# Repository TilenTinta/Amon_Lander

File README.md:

# Amon Lander Project

**Project Status:** In Progress

**Short description:** An open‑source EDF‑hovering lander/hopper inspired by **Sprite** (BPS.space)

> Part of the Amon Lander project:
>
> - **Amon Board** — flight controller hardware & firmware  
>   https://github.com/TilenTinta/Amon_Board
> - **Amon Link** — PC - drone RF bridge (PCB & firmware)  
>   https://github.com/TilenTinta/Amon_Link
> - **Amon Ground Control** — desktop GCS for telemetry & control  
>   https://github.com/TilenTinta/Amon_GroundControl_Software

---

## Table of Contents

- [Overview](#overview)
- [System Concept](#system-concept)
- [Hardware](#hardware)
  - [Frame](#frame)
  - [LED Boards](#led-boards)
- [Getting Started](#getting-started)
  - [Print & Materials](#print--materials)
  - [Assembly Notes](#assembly-notes)
- [Calibration & Testing](#calibration--testing)
- [Repository Structure](#repository-structure)
- [Roadmap](#roadmap)
- [Status & Disclaimer](#status--disclaimer)
- [License](#license)
- [Acknowledgments](#acknowledgments)

---

## Overview

Amon Lander is an educational lander/hopper platform designed to demonstrate vertical takeoff/landing and attitude control with thrust‑vectoring fins. The project emphasizes **building everything from scratch** and using mostly **free maker‑friendly tools**.

> [!INFO]
> **First integrated flight test:** 30.06.2026
>
> The goal of this flight was to validate the complete system, including the airframe, electronics, communications, protocol, flight controller, and ground station and have some fun!

---

## System Concept

- **Propulsion:** Single **EDF fan** for hover.  
- **Control:** **Four servos** drives fins for stabilization (**TVC**).  
- **Sensing:** Onboard sensors monitor flight parameters.  
- **Flight Computer:** **Custom PCB** handles computation and comms with the ground computer.  
- **Ground Segment:** Desktop app for **monitoring and control**.

> The goal is to learn: electronics, 3D modeling, embedded/desktop software, reading documentation, flight mechanics, and control theory—while having fun. Many things could be done faster or simpler, but this project idea is learning and exploration.

---

## Hardware

### Frame

The frame is inspired by Sprite, with custom ideas and modifications. The entire airframe is provided in **STL** and **STEP** and is printable on a standard **FDM** printer.  
- Early prototypes used **XPETG**; later versions used **LW‑PLA** to reduce weight.  
- Frame on image is **not yet flight‑tested** (at least not autonomous flight).  
- Designed in **Autodesk Fusion 360 (Personal Use license)**.

### LED Boards

Compact PCBs with two LEDs (**red** and **white**) indicate system state. They are mounted on the leg ends and top tubes. Although each LED board has a screw hole, **adhesive is recommended** for attachment.

---

## Getting Started

### Print & Materials

- Slice **STL** parts per your printer’s capabilities.  
- Recommended filaments:
  - **LW‑PLA** (weight savings) or **PETG/XPETG** (durability).  
- Orient parts to maximize strength along load paths (legs, fins, mounts).

### Assembly Notes

- Dry‑fit major components before final fastening/adhesive.  
- Verify servo travel and linkage geometry with power **off** first.  
- Route wiring to avoid EDF ingestion and moving fin linkages.  

---

## Calibration & Testing

- Bench‑test **sensors** and **servo directions** before powering the EDF.  
- Perform staged tests: electronics bring‑up → servo only → tethered hover.  
- Log telemetry and review for oscillations; tune control gains incrementally.  

### Test stand
For each test there is a separate test stand. There are:
- Thrust stand (test of EDF thrust level)
- Servo stand (test of servo rotation)
- One and two DoF stand (test of drone moments and fin deflection effect)

All tests are done with the help of an Arduino Uno board used for collecting data from sensors. At the same time, a connection over UART-USB is established to a drone for direct communication and command transmission. Everything is monitored by Jupyter scripts for easy and quick tests. Results are saved in **.csv** files for easy future analysis.

---

## Control algorithm
The initial plan was to use **Matlab** with **Simulink** to create a complete mathematical model of the drone. After further research, I found that many different methods could be used for controlling a drone like this. After designing the first model in **Simulink** and experimenting with the **Simulink Coder** plugin — with the idea of converting it to standard C code for use on my flight controller — I abandoned this approach. The complete model was then rewritten in **Python** using the **NumPy** library, which is used to test, tune, and further refine the drone model. This same model was subsequently rewritten in **CasADi** style, inheriting the **NumPy** parameters. It is still used in Python, but now with the **acados** framework and optimizer to export the complete control code directly to my MCU/flight controller.

Links to libraries:
- **CasADi**: https://github.com/casadi/casadi
- **acados**: https://github.com/acados/acados

---

## Status & Disclaimer

**In active development.** Designs and documents are evolving; expect changes and rough edges. Exercise caution when testing EDF propulsion and keep bystanders at a safe distance.

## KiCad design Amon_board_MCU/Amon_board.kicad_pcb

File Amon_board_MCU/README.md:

Amon Lander - Flight controller

Flight controler (MCU only version). It is 4-layer PCB with:<br />
- Grounged mounting holes
- Two XT60 power connectors
- Voltage measuring: board power and EDF battery voltage
- Input protection: reverse polarity protection - diode
- Max. input voltage: 12V (tested)
- Two buck conterters: 3V3 (MCU, sensors...) and 5V (servos) - both are capable of ~5A
- Board can be turned on when battery is connected or with switch wired to terminal 
- Sensors: Gyroscope (MPU6050), Temperature/Pressure/Humidity (BME280), TOF (TOF400C-VL53L1X) connector, Compas (HMC5883L)
- Radios: 2x NRF24L01+PA/LNA (RX-TX)
- GPS: GY-NEO6MV2 connector [same connector used for drone calibration - process described in firmware]
- On board RGB LED for status indication
- PWM: 4x servo, 1x EDF (can be configured differently)
- Additional external connectors for SPI and I2C devices
- MCU: STM32F405RGT6-LQFP64
- External flash for saving telemetry data
- SD card holder (additional data storing device)
- 10-pin JTAG programming connector
- USB OTG with surge protection

*PCB works but it will be replaced/upgraded to a newer version.

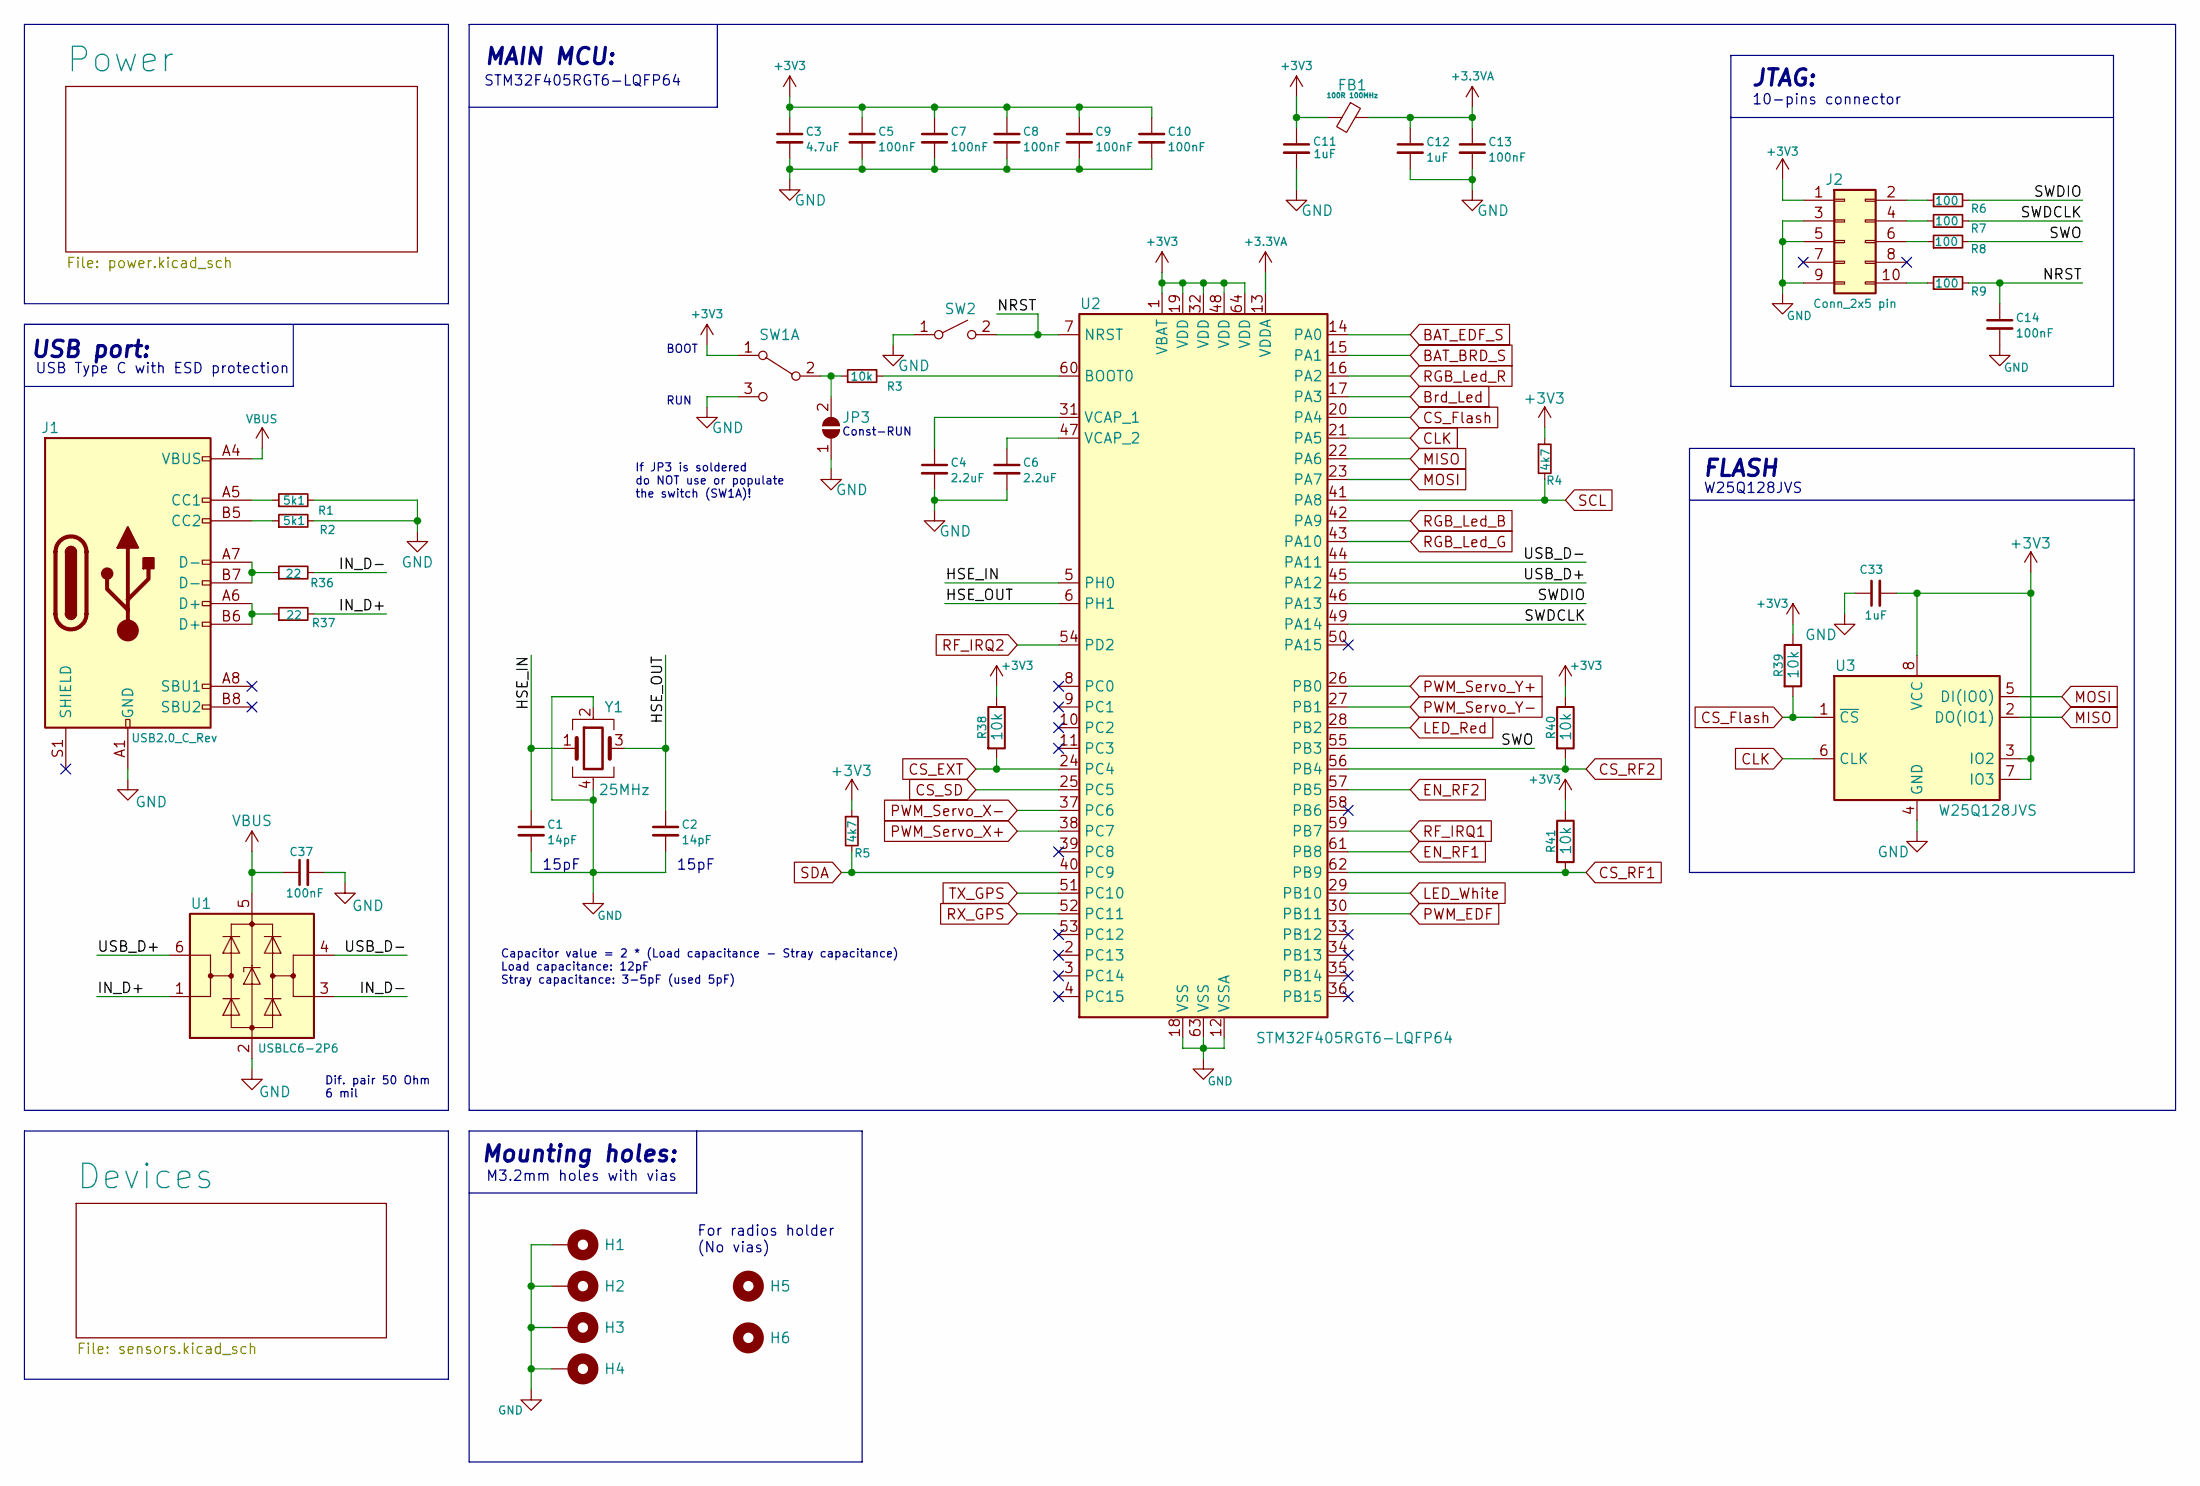
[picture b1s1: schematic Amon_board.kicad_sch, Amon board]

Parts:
C1, C2: 14pF; C_0603_1608Metric
C3: 4.7uF; C_0603_1608Metric
C4, C6: 2.2uF; C_0603_1608Metric
C5, C7, C8, C9, C10, C13, C14, C37: 100nF; C_0603_1608Metric
C11, C12, C33: 1uF; C_0603_1608Metric
FB1: 100R 100MHz; L_1206_3216Metric_Pad1.22x1.90mm_HandSolder
H1, H2, H3, H4: MountingHole_Pad; MountingHole_3.2mm_M3_Pad_Via
H5, H6: MountingHole; MountingHole_3.2mm_M3
J1: USB2.0_C_Rev; USB_C_Receptacle_XKB_U262-16XN-4BVC11
J2: Conn_2x5 pin; IDC-Header_2x05_P2.54mm_Vertical
JP3: SolderJumper_2_Open; SolderJumper-2_P1.3mm_Open_TrianglePad1.0x1.5mm
R1, R2: 5k1; R_0603_1608Metric
R3, R38, R39, R40, R41: 10k; R_0603_1608Metric
R4, R5: 4k7; R_0603_1608Metric
R6, R7, R8, R9: 100; R_0603_1608Metric
R36, R37: 22; R_0603_1608Metric
SW1: SW_DPDT; SW_SPDT_PCM12
SW2: SW_SPST; SW_Push_1P1T_NO_CK_KMR2
U1: USBLC6-2P6; SOT-23-6_Handsoldering
U2: STM32F405RGT6-LQFP64; LQFP-64_10x10mm_P0.5mm
U3: W25Q128JVS; SOIC-8_5.23x5.23mm_P1.27mm
Y1: 25MHz; Crystal_SMD_3225-4Pin_3.2x2.5mm

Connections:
+3.3VA: C12.1, C13.1, FB1.1, U2.13 (VDDA)
+3V3: C3.1, C5.1, C7.1, C8.1, C9.1, C10.1, C11.1, C33.2, FB1.2, J2.1, R4.1, R5.1, R38.1, R39.1, R40.1, R41.1, SW1.1 (A), U2.1 (VBAT), U2.19 (VDD), U2.32 (VDD), U2.48 (VDD), U2.64 (VDD), U3.3 (IO2), U3.7 (IO3), U3.8 (VCC); also elsewhere on the board
/HSE_IN: C1.1, U2.5 (PH0), Y1.1
/HSE_OUT: C2.1, U2.6 (PH1), Y1.3
/IN_D+: R37.2, U1.1 (I/O1)
/IN_D-: R36.2, U1.3 (I/O2)
/NRST: C14.1, R9.2, SW2.2 (B), U2.7 (NRST)
/SWDCLK: R7.2, U2.49 (PA14)
/SWDIO: R6.2, U2.46 (PA13)
/SWO: R8.2, U2.55 (PB3)
/USB_D+: U1.6 (I/O1), U2.45 (PA12)
/USB_D-: U1.4 (I/O2), U2.44 (PA11)
BAT_BRD_S: U2.15 (PA1); also elsewhere on the board
BAT_EDF_S: U2.14 (PA0); also elsewhere on the board
Brd_Led: U2.17 (PA3); also elsewhere on the board
CLK: U2.21 (PA5), U3.6 (CLK); also elsewhere on the board
CS_EXT: R38.2, U2.24 (PC4); also elsewhere on the board
CS_Flash: R39.2, U2.20 (PA4), U3.1 (~CS)
CS_RF1: R41.2, U2.62 (PB9); also elsewhere on the board
CS_RF2: R40.2, U2.56 (PB4); also elsewhere on the board
CS_SD: U2.25 (PC5); also elsewhere on the board
EN_RF1: U2.61 (PB8); also elsewhere on the board
EN_RF2: U2.57 (PB5); also elsewhere on the board
GND: C1.2, C2.2, C3.2, C4.2, C5.2, C6.2, C7.2, C8.2, C9.2, C10.2, C11.2, C12.2, C13.2, C14.2, C33.1, C37.2, H1.1, H2.1, H3.1, H4.1, J1.A1 (GND), J1.A12 (GND), J1.B1 (GND), J1.B12 (GND), J2.3, J2.5, J2.9, JP3.1 (A), R1.2, R2.2, SW1.3 (C), SW2.1 (A), U1.2 (GND), U2.12 (VSSA), U2.18 (VSS), U2.63 (VSS), U3.4 (GND), Y1.2, Y1.4; also elsewhere on the board
LED_Red: U2.28 (PB2); also elsewhere on the board
LED_White: U2.29 (PB10); also elsewhere on the board
MISO: U2.22 (PA6), U3.2 (DO(IO1)); also elsewhere on the board
MOSI: U2.23 (PA7), U3.5 (DI(IO0)); also elsewhere on the board
unnamed: J1.A5 (CC1), R1.1
unnamed: J1.B5 (CC2), R2.1
unnamed: J1.A6 (D+), J1.B6 (D+), R37.1
unnamed: J1.A7 (D-), J1.B7 (D-), R36.1
unnamed: J2.2, R6.1
unnamed: J2.4, R7.1
unnamed: J2.6, R8.1
unnamed: J2.10, R9.1
unnamed: JP3.2 (B), R3.1, SW1.2 (B)
unnamed: R3.2, U2.60 (BOOT0)
unnamed: C4.1, U2.31 (VCAP_1)
unnamed: C6.1, U2.47 (VCAP_2)
PWM_EDF: U2.30 (PB11); also elsewhere on the board
PWM_Servo_X+: U2.38 (PC7); also elsewhere on the board
PWM_Servo_X-: U2.37 (PC6); also elsewhere on the board
PWM_Servo_Y+: U2.26 (PB0); also elsewhere on the board
PWM_Servo_Y-: U2.27 (PB1); also elsewhere on the board
RF_IRQ1: U2.59 (PB7); also elsewhere on the board
RF_IRQ2: U2.54 (PD2); also elsewhere on the board
RGB_Led_B: U2.42 (PA9); also elsewhere on the board
RGB_Led_G: U2.43 (PA10); also elsewhere on the board
RGB_Led_R: U2.16 (PA2); also elsewhere on the board
RX_GPS: U2.52 (PC11); also elsewhere on the board
SCL: R4.2, U2.41 (PA8); also elsewhere on the board
SDA: R5.2, U2.40 (PC9); also elsewhere on the board
TX_GPS: U2.51 (PC10); also elsewhere on the board
VBUS: C37.1, J1.A4 (VBUS), J1.A9 (VBUS), J1.B4 (VBUS), J1.B9 (VBUS), U1.5 (VBUS)

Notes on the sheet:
15pF
W25Q128JVS
10-pins connector
If JP3 is soldered do NOT use or populate the switch (SW1A)!
Capacitor value = 2 * (Load capacitance - Stray capacitance) Load capacitance: 12pF Stray capacitance: 3-5pF (used 5pF)
RUN
JTAG:
M3.2mm holes with vias
Dif. pair 50 Ohm 6 mil
USB port:
Const-RUN
FLASH
Mounting holes:
MAIN MCU:
USB Type C with ESD protection
BOOT
For radios holder (No vias)
STM32F405RGT6-LQFP64

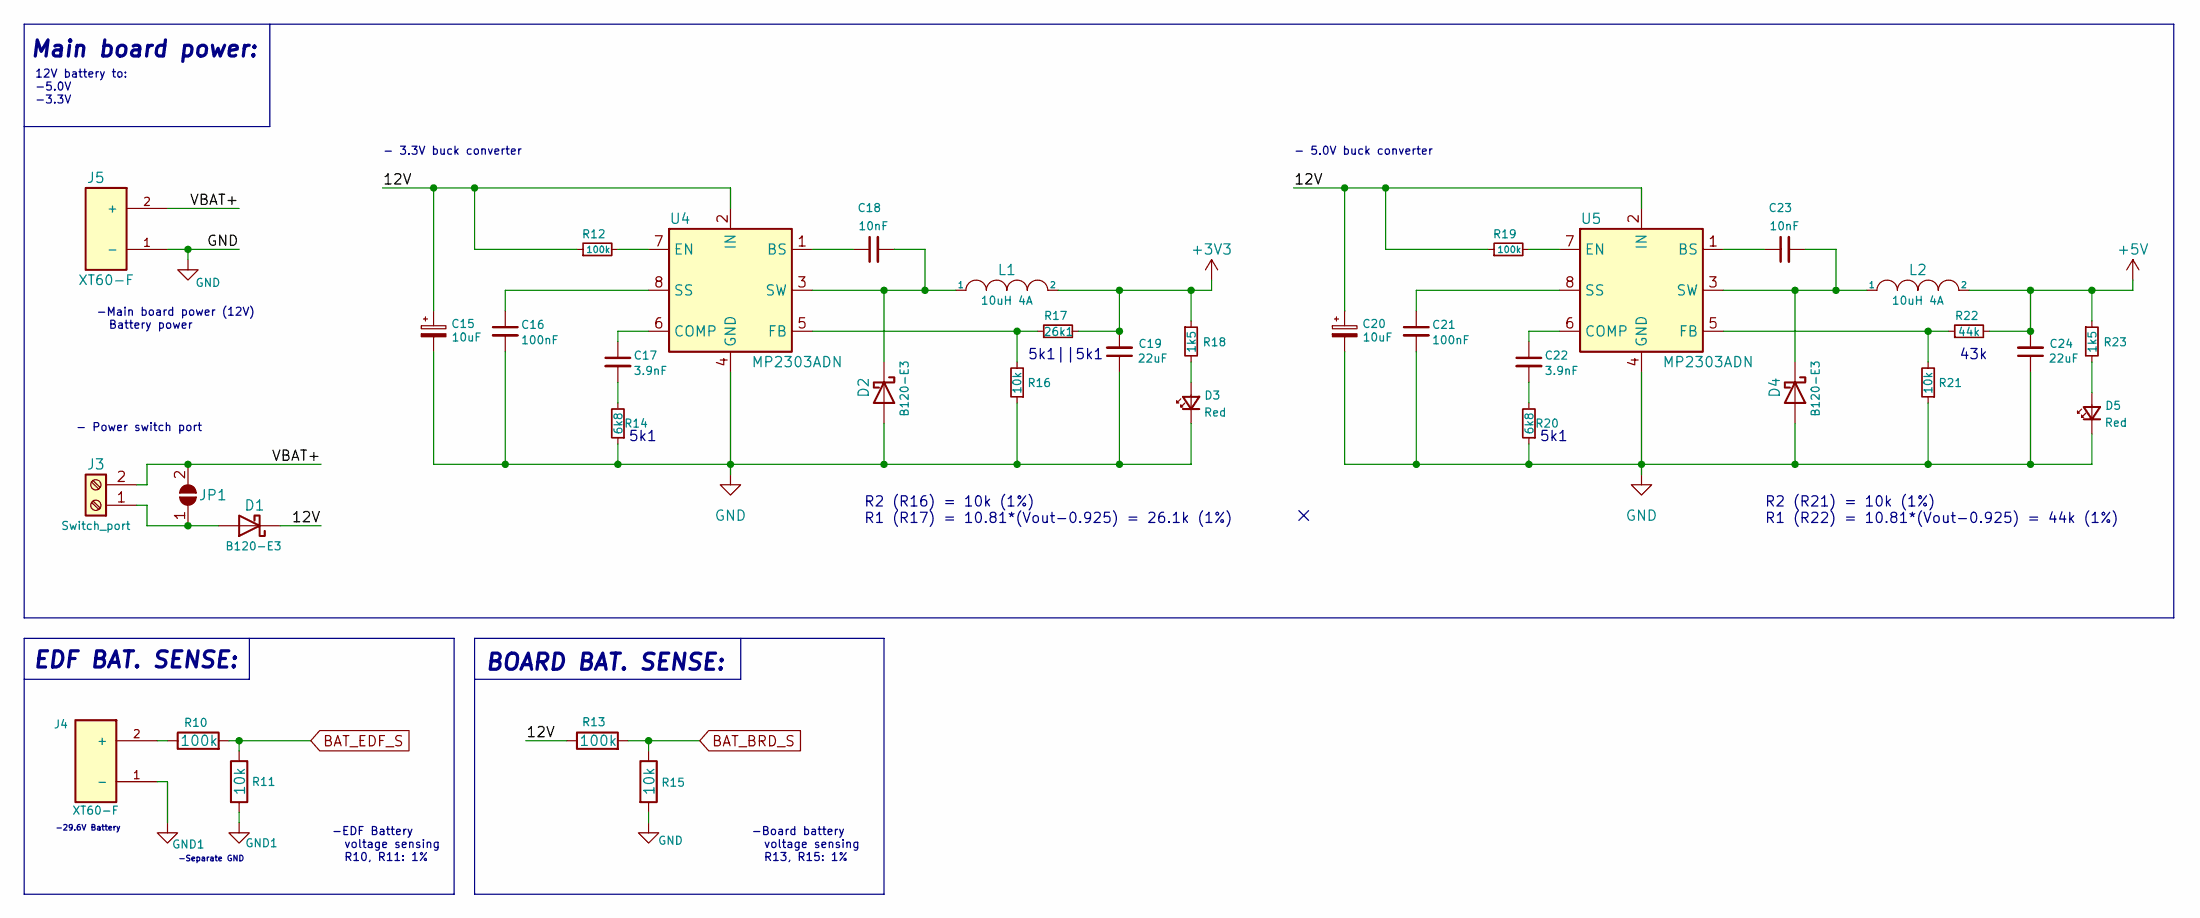
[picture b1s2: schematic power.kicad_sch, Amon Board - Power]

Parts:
C15, C20: 10uF; CP_EIA-3216-10_Kemet-I
C16, C21: 100nF; C_0603_1608Metric
C17, C22: 3.9nF; C_0603_1608Metric
C18, C23: 10nF; C_0603_1608Metric
C19, C24: 22uF; C_1206_3216Metric
D1, D2, D4: B120-E3; D_SMA
D3, D5: Red; LED_0603_1608Metric
J3: Switch_port; TerminalBlock_MetzConnect_Type055_RT01502HDWU_1x02_P5.00mm_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
J4, J5: XT60-F; AMASS_XT60-M; PARTREV 1.2
JP1: SolderJumper_2_Open; SolderJumper-2_P1.3mm_Open_Pad1.0x1.5mm
L1, L2: 10uH 4A; L_10.4x10.4_H4.8
R10, R13: 100k; R_1206_3216Metric
R11, R15: 10k; R_1206_3216Metric
R12, R19: 100k; R_0603_1608Metric
R14, R20: 6k8; R_0603_1608Metric
R16, R21: 10k; R_0603_1608Metric
R17: 26k1; R_0603_1608Metric
R18, R23: 1k5; R_0603_1608Metric
R22: 44k; R_0603_1608Metric
U4, U5: MP2303ADN; SOIC-8-1EP_3.9x4.9mm_P1.27mm_EP2.62x3.51mm

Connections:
+3V3: C19.2, L1.2, R17.2, R18.1; also elsewhere on the board
+5V: C24.2, L2.2, R22.2, R23.1; also elsewhere on the board
/Power/12V: C15.1, C20.1, D1.1 (K), R12.1, R13.1, R19.1, U4.2 (IN), U5.2 (IN)
/Power/VBAT+: J3.2, J5.2 (+), JP1.2 (B)
BAT_BRD_S: R13.2, R15.1; also elsewhere on the board
BAT_EDF_S: R10.2, R11.1; also elsewhere on the board
GND: C15.2, C16.2, C19.1, C20.2, C21.2, C24.1, D2.2 (A), D3.1 (K), D4.2 (A), D5.1 (K), J5.1 (-), R14.1, R15.2, R16.1, R20.1, R21.1, U4.4 (GND), U5.4 (GND); also elsewhere on the board
GND1: J4.1 (-), R11.2
unnamed: C17.2, R14.2
unnamed: C22.2, R20.2
unnamed: D1.2 (A), J3.1, JP1.1 (A)
unnamed: C18.2, D2.1 (K), L1.1, U4.3 (SW)
unnamed: D3.2 (A), R18.2
unnamed: C23.2, D4.1 (K), L2.1, U5.3 (SW)
unnamed: D5.2 (A), R23.2
unnamed: J4.2 (+), R10.1
unnamed: C18.1, U4.1 (BS)
unnamed: C17.1, U4.6 (COMP)
unnamed: R12.2, U4.7 (EN)
unnamed: R16.2, R17.1, U4.5 (FB)
unnamed: C16.1, U4.8 (SS)
unnamed: C23.1, U5.1 (BS)
unnamed: C22.1, U5.6 (COMP)
unnamed: R19.2, U5.7 (EN)
unnamed: R21.2, R22.1, U5.5 (FB)
unnamed: C21.1, U5.8 (SS)

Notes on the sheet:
-Board battery voltage sensing R13, R15: 1%
5k1||5k1
-Separate GND
-Main board power (12V) Battery power
5k1
- 5.0V buck converter
BOARD BAT. SENSE:
-29.6V Battery
-EDF Battery voltage sensing R10, R11: 1%
12V battery to: -5.0V -3.3V
- 3.3V buck converter
- Power switch port
EDF BAT. SENSE:
R2 (R21) = 10k (1%) R1 (R22) = 10.81*(Vout-0.925) = 44k (1%)
43k
Main board power:
R2 (R16) = 10k (1%) R1 (R17) = 10.81*(Vout-0.925) = 26.1k (1%)

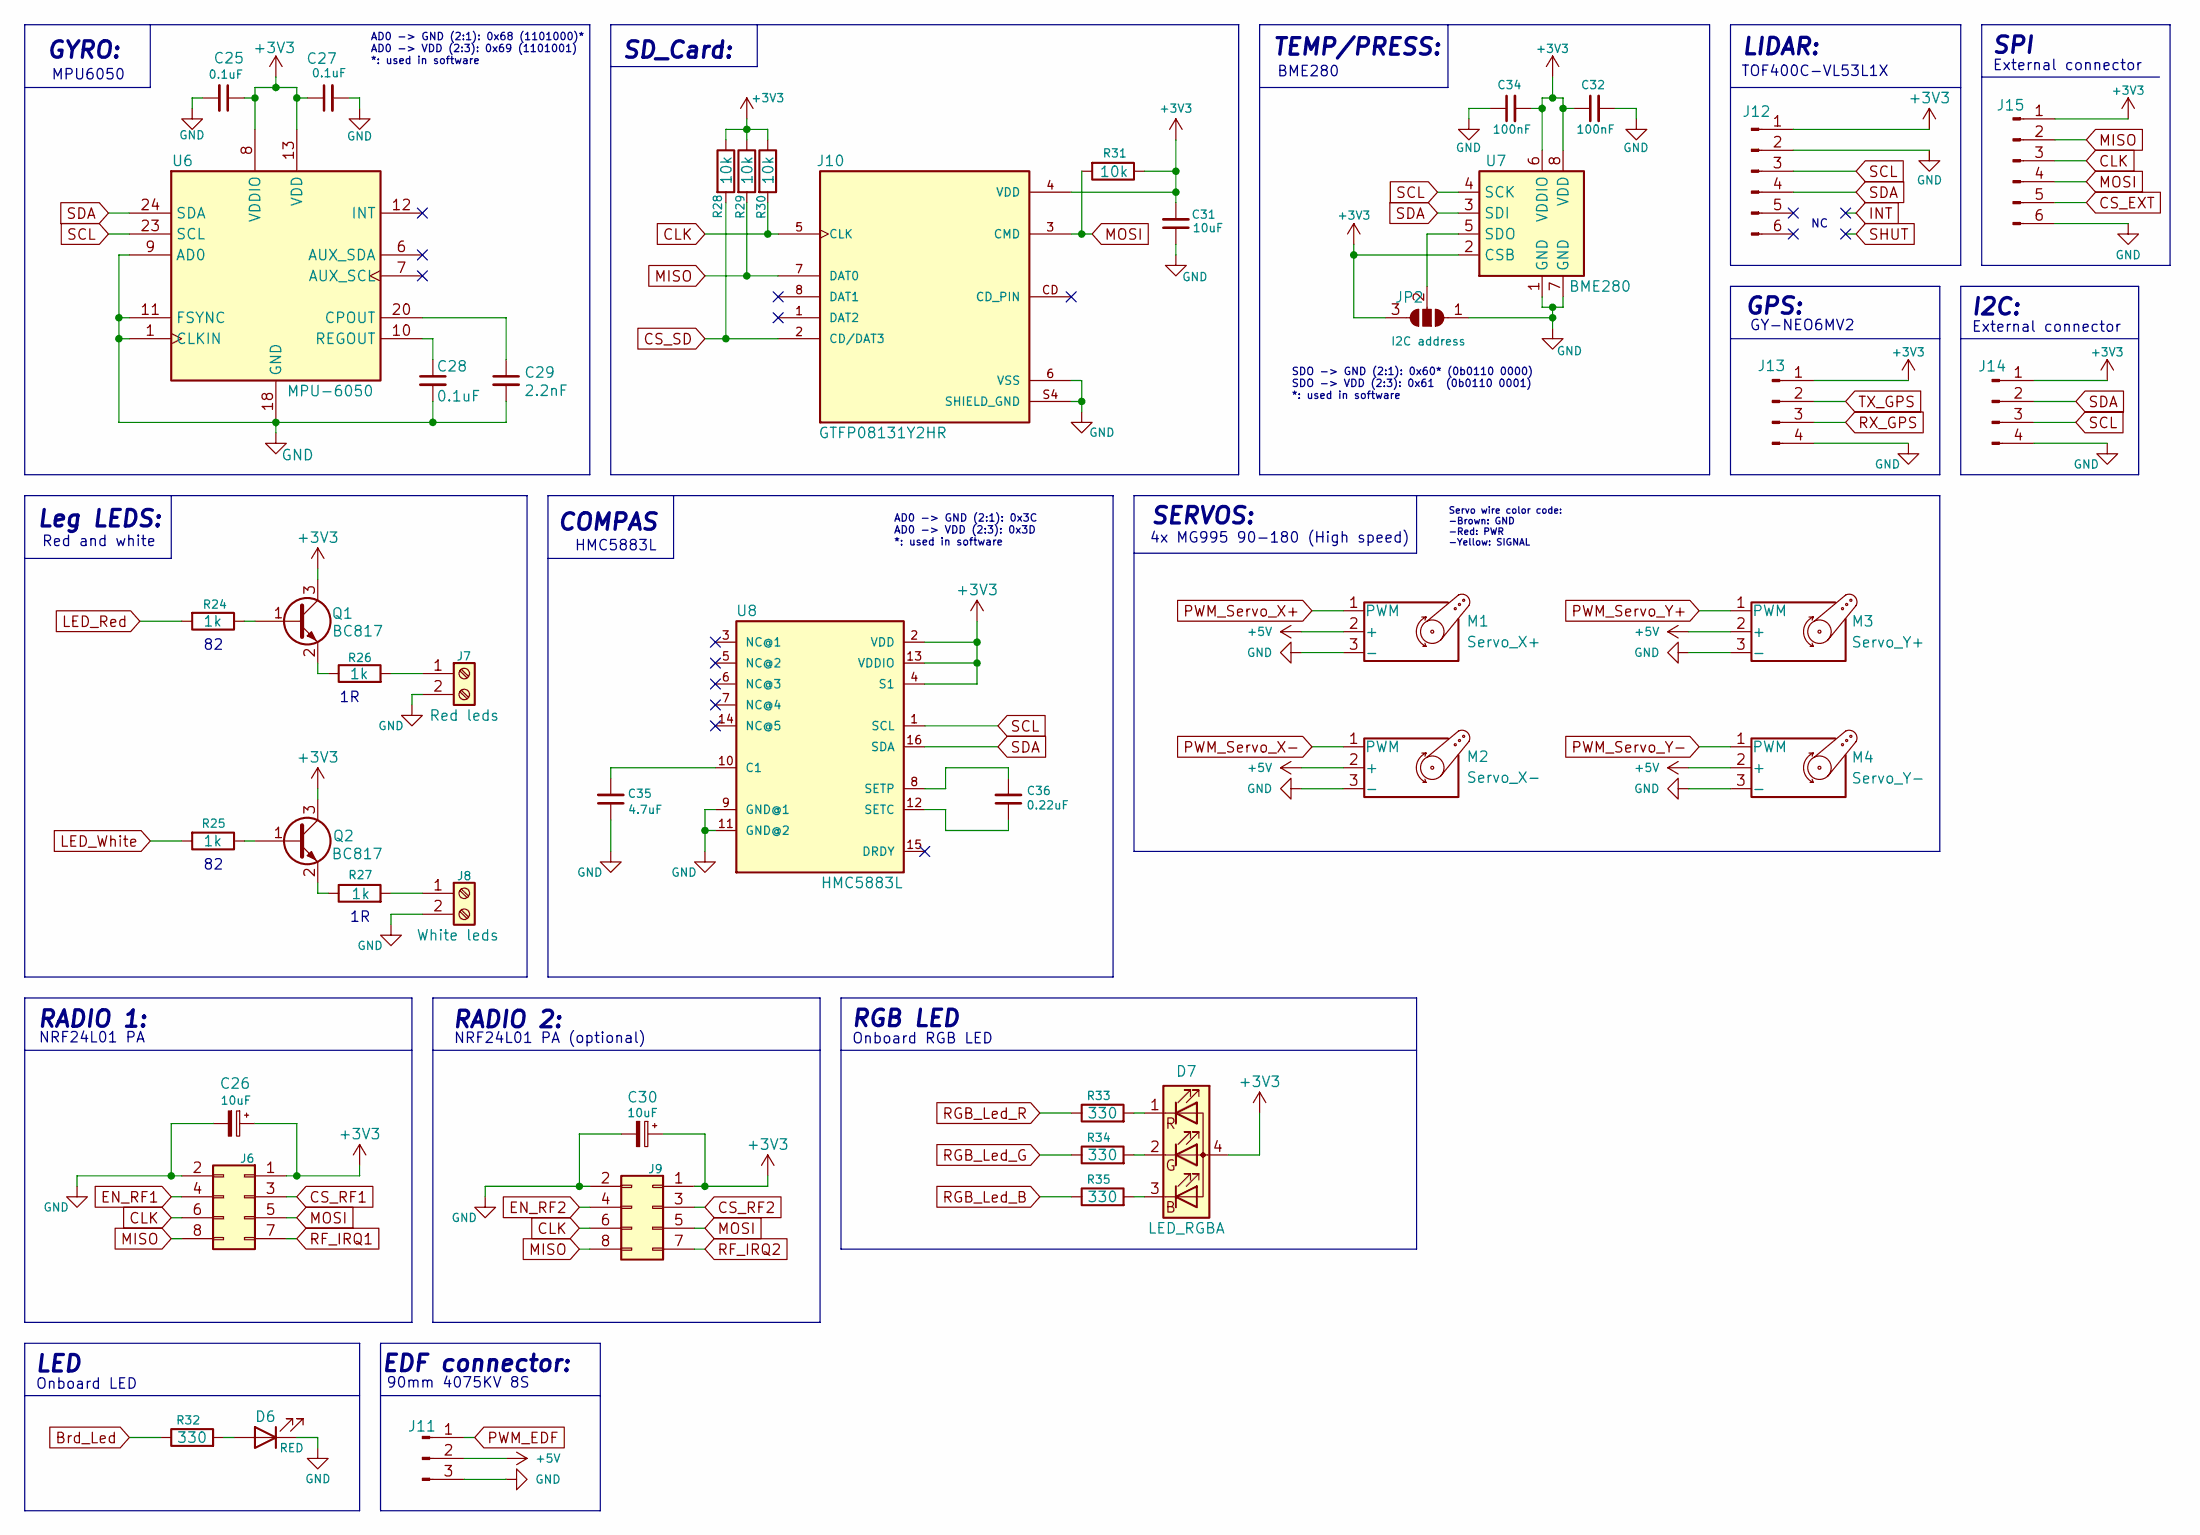
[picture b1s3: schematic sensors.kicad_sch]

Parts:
C25, C27, C28: 0.1uF; C_0603_1608Metric
C26, C30: 10uF; CP_Elec_4x5.4
C29: 2.2nF; C_0603_1608Metric
C31: 10uF; C_0603_1608Metric
C32, C34: 100nF; C_0603_1608Metric
C35: 4.7uF; C_0603_1608Metric
C36: 0.22uF; C_0603_1608Metric
D6: RED; LED_0603_1608Metric
D7: LED_RGBA; LED_Cree-PLCC4_3.2x2.8mm_CCW
J6, J9: Conn_02x04_Odd_Even; PinSocket_2x04_P2.54mm_Vertical
J7: Red leds; TerminalBlock_MetzConnect_Type055_RT01502HDWU_1x02_P5.00mm_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
J8: White leds; TerminalBlock_MetzConnect_Type055_RT01502HDWU_1x02_P5.00mm_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
J10: GTFP08131Y2HR; AMPHENOL_GTFP08131Y2HR; PARTREV A
J11: Conn_01x03_Male; PinHeader_1x03_P2.54mm_Vertical
J12: Conn_01x06_Male; JST_XH_S6B-XH-A-1_1x06_P2.50mm_Horizontal
J13: Conn_01x04_Male; JST_XH_S4B-XH-A_1x04_P2.50mm_Horizontal
J14: Conn_01x04_Male; PinHeader_1x04_P2.54mm_Vertical
J15: Conn_01x06_Male; PinHeader_1x06_P2.54mm_Vertical
JP2: I2C address; SolderJumper-3_P1.3mm_Open_RoundedPad1.0x1.5mm_NumberLabels
M1: Servo_X+; PinHeader_1x03_P2.54mm_Vertical
M2: Servo_X-; PinHeader_1x03_P2.54mm_Vertical
M3: Servo_Y+; PinHeader_1x03_P2.54mm_Vertical
M4: Servo_Y-; PinHeader_1x03_P2.54mm_Vertical
Q1, Q2: BC817; SOT-23
R24, R25, R26, R27: 1k; R_0603_1608Metric
R28, R29, R30, R31: 10k; R_0603_1608Metric
R32, R33, R34, R35: 330; R_0603_1608Metric
U6: MPU-6050; InvenSense_QFN-24_4x4mm_P0.5mm
U7: BME280; Bosch_LGA-8_2x2.5mm_P0.65mm_ClockwisePinNumbering
U8: HMC5883L; LPCC-16

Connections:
+3V3: C25.1, C26.1, C27.1, C30.1, C31.2, C32.1, C34.2, D7.4 (A), J6.1, J9.1, J10.4 (VDD), J12.1, J13.1, J14.1, J15.1, JP2.3 (B), Q1.3 (C), Q2.3 (C), R28.1, R29.1, R30.1, R31.1, U6.8 (VDDIO), U6.13 (VDD), U7.2 (CSB), U7.6 (VDDIO), U7.8 (VDD), U8.2 (VDD), U8.4 (S1), U8.13 (VDDIO); also elsewhere on the board
+5V: J11.2, M1.2 (+), M2.2 (+), M3.2 (+), M4.2 (+); also elsewhere on the board
Brd_Led: R32.1; also elsewhere on the board
CLK: J6.6, J9.6, J10.5 (CLK), J15.3, R30.2; also elsewhere on the board
CS_EXT: J15.5; also elsewhere on the board
CS_RF1: J6.3; also elsewhere on the board
CS_RF2: J9.3; also elsewhere on the board
CS_SD: J10.2 (CD/DAT3), R28.2; also elsewhere on the board
EN_RF1: J6.4; also elsewhere on the board
EN_RF2: J9.4; also elsewhere on the board
GND: C25.2, C26.2, C27.2, C28.2, C29.2, C30.2, C31.1, C32.2, C34.1, C35.1, D6.1 (K), J6.2, J7.2, J8.2, J9.2, J10.6 (VSS), J10.S4 (SHIELD_GND), J11.3, J12.2, J13.4, J14.4, J15.6, JP2.1 (A), M1.3 (-), M2.3 (-), M3.3 (-), M4.3 (-), U6.1 (CLKIN), U6.9 (AD0), U6.11 (FSYNC), U6.18 (GND), U7.1 (GND), U7.7 (GND), U8.9 (GND@1), U8.11 (GND@2); also elsewhere on the board
LED_Red: R24.2; also elsewhere on the board
LED_White: R25.2; also elsewhere on the board
MISO: J6.8, J9.8, J10.7 (DAT0), J15.2, R29.2; also elsewhere on the board
MOSI: J6.5, J9.5, J10.3 (CMD), J15.4, R31.2; also elsewhere on the board
unnamed: D6.2 (A), R32.2
unnamed: D7.3 (BK), R35.2
unnamed: D7.2 (GK), R34.2
unnamed: D7.1 (RK), R33.2
unnamed: J7.1, R26.2
unnamed: J8.1, R27.2
unnamed: JP2.2 (C), U7.5 (SDO)
unnamed: Q1.1 (B), R24.1
unnamed: Q1.2 (E), R26.1
unnamed: Q2.1 (B), R25.1
unnamed: Q2.2 (E), R27.1
unnamed: C29.1, U6.20 (CPOUT)
unnamed: C28.1, U6.10 (REGOUT)
unnamed: C35.2, U8.10 (C1)
unnamed: C36.1, U8.12 (SETC)
unnamed: C36.2, U8.8 (SETP)
PWM_EDF: J11.1; also elsewhere on the board
PWM_Servo_X+: M1.1 (PWM); also elsewhere on the board
PWM_Servo_X-: M2.1 (PWM); also elsewhere on the board
PWM_Servo_Y+: M3.1 (PWM); also elsewhere on the board
PWM_Servo_Y-: M4.1 (PWM); also elsewhere on the board
RF_IRQ1: J6.7; also elsewhere on the board
RF_IRQ2: J9.7; also elsewhere on the board
RGB_Led_B: R35.1; also elsewhere on the board
RGB_Led_G: R34.1; also elsewhere on the board
RGB_Led_R: R33.1; also elsewhere on the board
RX_GPS: J13.3; also elsewhere on the board
SCL: J12.3, J14.3, U6.23 (SCL), U7.4 (SCK), U8.1 (SCL); also elsewhere on the board
SDA: J12.4, J14.2, U6.24 (SDA), U7.3 (SDI), U8.16 (SDA); also elsewhere on the board
TX_GPS: J13.2; also elsewhere on the board

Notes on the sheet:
COMPAS
Red and white
Leg LEDS:
GYRO:
External connector
90mm 4075KV 8S
SPI
AD0 -> GND (2:1): 0x3C AD0 -> VDD (2:3): 0x3D *: used in software
I2C:
TOF400C-VL53L1X
Onboard RGB LED
GY-NEO6MV2
TEMP/PRESS:
AD0 -> GND (2:1): 0x68 (1101000)* AD0 -> VDD (2:3): 0x69 (1101001) *: used in software
SERVOS:
4x MG995 90-180 (High speed)
NRF24L01 PA
LED
RADIO 1:
LIDAR:
Onboard LED
HMC5883L
RGB LED
SD_Card:
EDF connector:
NRF24L01 PA (optional)
Servo wire color code: -Brown: GND -Red: PWR -Yellow: SIGNAL
GPS:
SDO -> GND (2:1): 0x60* (0b0110 0000) SDO -> VDD (2:3): 0x61 (0b0110 0001) *: used in software
MPU6050
BME280
RADIO 2:

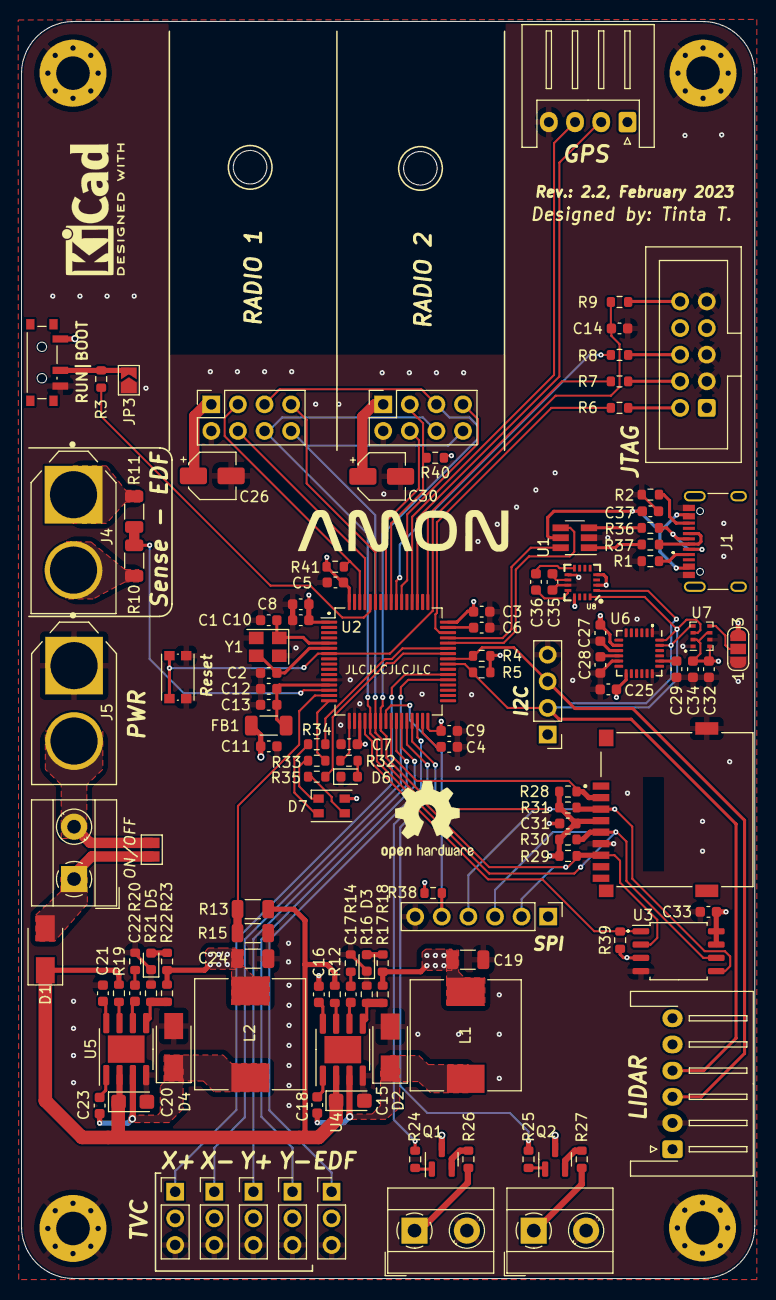
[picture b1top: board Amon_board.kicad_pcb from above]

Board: 4 copper layers, 70.0 x 120.0 mm, 129 parts (0 on the bottom side), 93 nets.

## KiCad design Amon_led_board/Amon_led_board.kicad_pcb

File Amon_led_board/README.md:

Amon Lander - LED board

Everyone knows that no project is correctly done without some LEDs. For that case the drone uses small PCBs with two LED lights (red and white) that light accordingly with the state of drone. They are mounted at the end of landing legs and top pipes. Even thou they include hole and can be screwd in the holder the gluing is more recomended

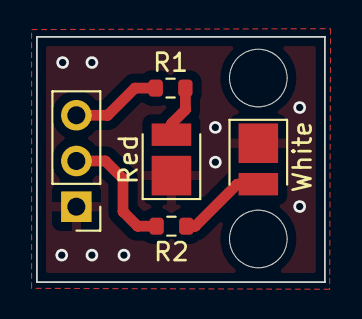
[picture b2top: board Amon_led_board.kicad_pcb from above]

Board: 2 copper layers, 16.0 x 13.6 mm, 5 parts (0 on the bottom side), 5 nets.

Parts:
J1: 3_Pin_Male; PinHeader_1x03_P2.54mm_Vertical
R1, R2: 40 Ohm; R_0603_1608Metric
Red: RED; LED_PLCC_2835
White: WHITE; LED_PLCC_2835

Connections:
GND: J1.1, Red.1 (K), White.1 (K)
unnamed: R1.2, Red.2 (A)
unnamed: R2.2, White.2 (A)
unnamed: J1.2, R2.1
unnamed: J1.3, R1.1

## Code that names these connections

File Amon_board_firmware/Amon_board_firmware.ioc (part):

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Mcu.Name=STM32F405RGTx
Mcu.Package=LQFP64
Mcu.UserName=STM32F405RGTx
PA0-WKUP.GPIOParameters=GPIO_Label
PA0-WKUP.GPIO_Label=EDF_BAT
PA0-WKUP.Signal=ADCx_IN0
PA1.GPIOParameters=GPIO_Label
PA1.GPIO_Label=BRD_BAT
PA1.Signal=ADCx_IN1
PA10.GPIOParameters=GPIO_Label
PA10.GPIO_Label=TIM1_CH3_RGB_R
PA10.Signal=S_TIM1_CH3
PA11.Mode=Device_Only
PA11.Signal=USB_OTG_FS_DM
PA12.Mode=Device_Only
PA12.Signal=USB_OTG_FS_DP
PA13.Mode=Trace_Asynchronous_SW
PA13.Signal=SYS_JTMS-SWDIO
PA14.Mode=Trace_Asynchronous_SW
PA14.Signal=SYS_JTCK-SWCLK
PA2.GPIOParameters=GPIO_Label
PA2.GPIO_Label=TIM2_CH3_RGB_B
PA2.Signal=S_TIM2_CH3
PA3.GPIOParameters=GPIO_Label
PA3.GPIO_Label=LED_Brd
PA3.Signal=GPIO_Output
PA4.GPIOParameters=GPIO_Label
PA4.GPIO_Label=CS_Flash
PA4.Signal=GPIO_Output
PA5.Mode=Full_Duplex_Master
PA5.Signal=SPI1_SCK
PA6.Mode=Full_Duplex_Master
PA6.Signal=SPI1_MISO
PA7.Mode=Full_Duplex_Master
PA7.Signal=SPI1_MOSI
PA8.Mode=I2C
PA8.Signal=I2C3_SCL
PA9.GPIOParameters=GPIO_Label
PA9.GPIO_Label=TIM1_CH2_RGB_G
PA9.Signal=S_TIM1_CH2
PB0.GPIOParameters=GPIO_Label
PB0.GPIO_Label=TIM3_CH3_Y+
PB0.Signal=S_TIM3_CH3
PB1.GPIOParameters=GPIO_Label
PB1.GPIO_Label=TIM3_CH4_Y-
PB1.Signal=S_TIM3_CH4
PB10.GPIOParameters=GPIO_Label
PB10.GPIO_Label=LED_White
PB10.Signal=GPIO_Output
PB11.GPIOParameters=GPIO_Label
PB11.GPIO_Label=TIM2_CH4_EDF
PB11.Signal=S_TIM2_CH4
PB2.GPIOParameters=GPIO_Label
PB2.GPIO_Label=LED_Red
PB2.Signal=GPIO_Output
PB3.Mode=Trace_Asynchronous_SW
PB3.Signal=SYS_JTDO-SWO
PB4.GPIOParameters=GPIO_Label
PB4.GPIO_Label=CS_RF2
PB4.Signal=GPIO_Output
PB5.GPIOParameters=GPIO_Label
PB5.GPIO_Label=EN_RF2
PB5.Signal=GPIO_Output
PB7.GPIOParameters=GPIO_Label,GPIO_ModeDefaultEXTI
PB7.GPIO_Label=RF_IRQ1
PB7.GPIO_ModeDefaultEXTI=GPIO_MODE_IT_RISING
PB7.Signal=GPXTI7
PB8.GPIOParameters=GPIO_Label
PB8.GPIO_Label=EN_RF1
PB8.Signal=GPIO_Output
PB9.GPIOParameters=GPIO_Label
PB9.GPIO_Label=CS_RF1
PB9.Signal=GPIO_Output
PC10.GPIOParameters=GPIO_Label
PC10.GPIO_Label=UART4_TX_GPS
PC10.Mode=Asynchronous
PC10.Signal=UART4_TX
PC11.GPIOParameters=GPIO_Label
PC11.GPIO_Label=UART4_RX_GPS
PC11.Mode=Asynchronous
PC11.Signal=UART4_RX
PC4.GPIOParameters=GPIO_Label
PC4.GPIO_Label=CS_Ext
PC4.Signal=GPIO_Output
PC5.GPIOParameters=GPIO_Label
PC5.GPIO_Label=CS_SD
PC5.Signal=GPIO_Output
PC6.GPIOParameters=GPIO_Label
PC6.GPIO_Label=TIM3_CH1_X-
PC6.Signal=S_TIM3_CH1
PC7.GPIOParameters=GPIO_Label
PC7.GPIO_Label=TIM3_CH2_X+
PC7.Signal=S_TIM3_CH2
PC9.Mode=I2C
PC9.Signal=I2C3_SDA
PD2.GPIOParameters=GPIO_Label
PD2.GPIO_Label=RF_IRQ2
PD2.Signal=GPXTI2
PH0-OSC_IN.Mode=HSE-External-Oscillator
PH0-OSC_IN.Signal=RCC_OSC_IN
PH1-OSC_OUT.Mode=HSE-External-Oscillator
PH1-OSC_OUT.Signal=RCC_OSC_OUT
RCC.HSE_VALUE=25000000
RCC.SYSCLKFreq_VALUE=120000000
RCC.SYSCLKSource=RCC_SYSCLKSOURCE_PLLCLK
board=custom

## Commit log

2022-12-04 Added Amon led board
2022-12-04 Added: README-unfinished
2023-02-12 added Amon board and frame: both not last version
2023-03-14 PCB update, stl update (pcb holder)
2023-03-22 Desktop app Amon controll
2023-03-23 Amon controll COM, menu window
2023-03-29 updated stl, data, board update
2023-04-08 PCB repair: crystal footprint, radio connector fliped, text
2023-04-09 added Pictures
2023-04-09 Readme update
2023-04-10 picture replace
2023-04-20 board firmware - BME280, LED..
2023-06-26 changed directories
2023-06-26 repair
2023-06-26 Control update4
2023-06-26 added amon link code
2023-10-20 added pictires
2024-12-12 Update
    addes new images, filled and new READMEs, added pull-ups on PCB
2025-08-30 Update
    project separation
2025-08-30 Update
    readme
2026-01-21 Update
    readme update
2026-02-23 Update
    stm and step files fot optitrack markers mount
2026-03-01 Update
    additional software
2026-03-01 Update
    Kalman calibration code and test
2026-03-08 Update
    log parser and ploter
2026-03-25 Update
    finished test stand (frame and software) but untested, start of control model
2026-03-31 Update
    Matlab model in development
2026-04-01 Update
    Matlab model in development, model no errors
2026-04-26 Update: model converted from Simulink to Python for easyer future use of acados library
2026-05-03 Update: first test code for math model in casadi and acados
2026-05-04 Update: casadi and acados model finished, problem with solver not converging (omega to big for dt)
2026-05-06 Update: build of blasfeo and hpipm and recheck of casadi model, repair of gravity
2026-05-07 Update: virst working version of NMPC for height, stable optimization, warm-start, unoptimized for real model
2026-05-25 Update: first acados nmpc implementation complete, all libraries added
2026-06-11 Update: new file structure for nmpc, 50Hz to 100Hz, generated c code simulation
2026-06-14 Update: controll files, readme
2026-06-19 backup, blasfeo and hpipm for armv7
2026-06-30 Update: first flight (with a lot of help but baseline works)!
